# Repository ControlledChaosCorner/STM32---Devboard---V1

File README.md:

This Board uses an ST STM32F030C6T6TR MCU

Component list:

- 1 × 18pF capacitor (0603)
- 8 × 100nF capacitors (0603)
- 4 × 4.7µF capacitors (0603)
- 1 × 1nF capacitor (0603)
- 1 × 10µF capacitor (0805)
- 1 × 10nF capacitor (0603)
- 1 × 1µF capacitor (0805)
- 2 × LED (0603) — Power & PA15
- 1 × Fuse 1A (Plugin)
- 1 × USB Type-C receptacle (6-pin, power-only)
- 1 × SWD header (1×5, 2.54mm)
- 2 × Pin header (1×10, 2.54mm)
- 2 × Pin header (1×12, 2.54mm)
- 2 × 10k resistors (1206)
- 2 × 5.1k resistors (0603)
- 2 × 4.7k resistors (1206)
- 1 × 1.5k resistor (0603)
- 1 × 240Ω resistor (1206)
- 1 × Reset switch (SMD tactile)
- 1 × STM32F030C6 microcontroller (LQFP-48, 7×7mm, 0.5mm pitch)
- 1 × TLV70433 regulator (SOT-23-5)

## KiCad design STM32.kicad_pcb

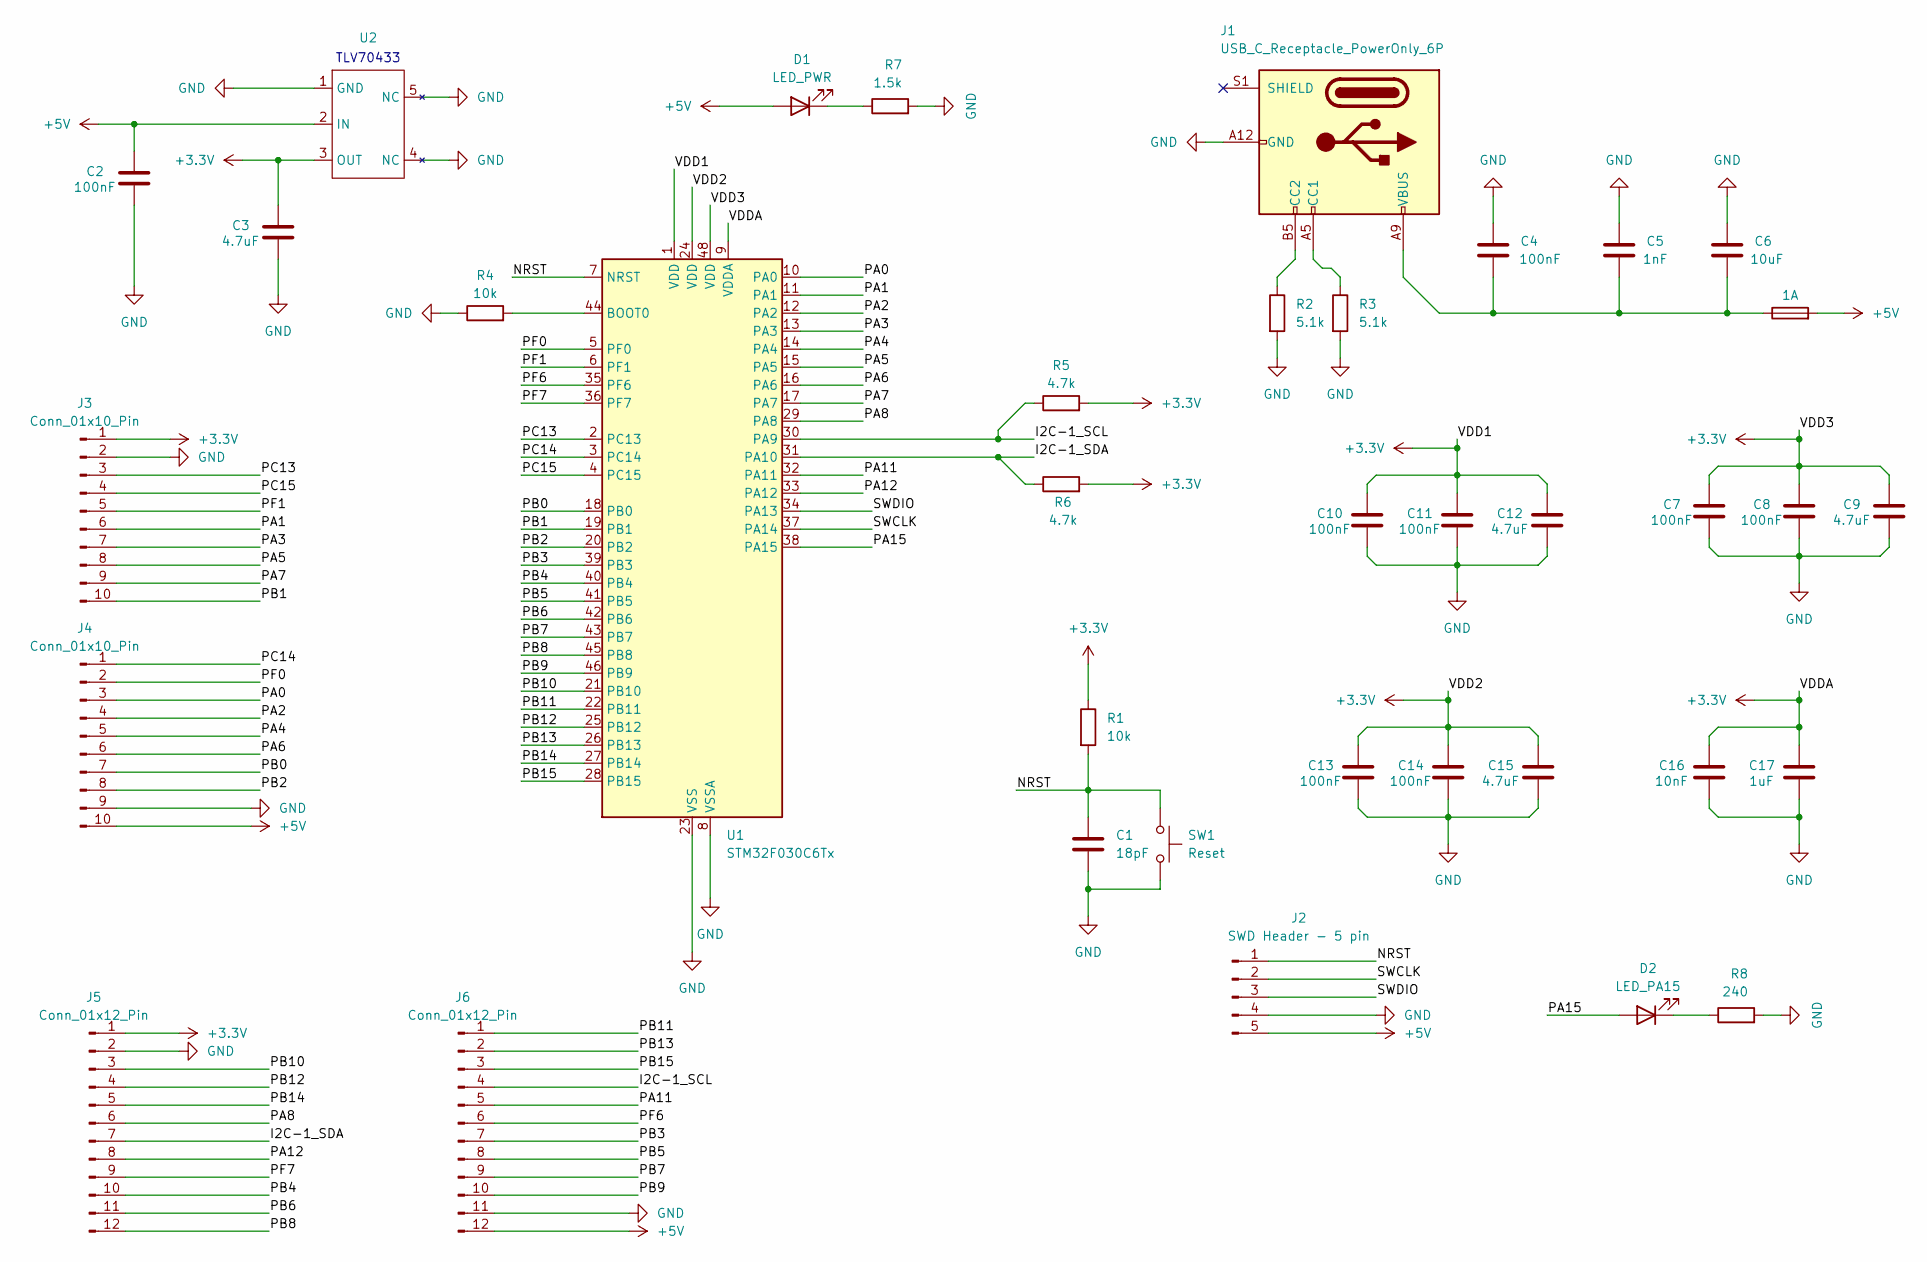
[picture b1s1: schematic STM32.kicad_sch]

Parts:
C1: 18pF; C_0603_1608Metric
C2, C4, C7, C8, C10, C11, C13, C14: 100nF; C_0603_1608Metric
C3, C9, C12, C15: 4.7uF; C_0603_1608Metric
C5: 1nF; C_0603_1608Metric
C6: 10uF; C_0805_2012Metric
C16: 10nF; C_0603_1608Metric
C17: 1uF; C_0805_2012Metric
D1: LED_PWR; LED_0603_1608Metric
D2: LED_PA15; LED_0603_1608Metric
F1: 1A; 1A Fuse
J1: USB_C_Receptacle_PowerOnly_6P; USB_C_Receptacle_GCT_USB4125-xx-x_6P_TopMnt_Horizontal
J2: SWD Header - 5 pin; PinHeader_1x05_P2.54mm_Vertical
J3, J4: Conn_01x10_Pin; PinHeader_1x10_P2.54mm_Vertical
J5, J6: Conn_01x12_Pin; PinHeader_1x12_P2.54mm_Vertical
R1, R4: 10k; R_1206_3216Metric
R2, R3: 5.1k; R_0603_1608Metric
R5, R6: 4.7k; R_1206_3216Metric
R7: 1.5k; R_0603_1608Metric
R8: 240; R_1206_3216Metric
SW1: Reset; SW_SPST_CK_RS282G05A3
U1: STM32F030C6Tx; LQFP-48_7x7mm_P0.5mm
U2: SOT-23-5

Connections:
+3.3V: C3.2, C7.2, C8.2, C9.2, C10.2, C11.2, C12.2, C13.2, C14.2, C15.2, C16.2, C17.2, J3.1, J5.1, R1.1, R5.2, R6.2, U1.1 (VDD), U1.9 (VDDA), U1.24 (VDD), U1.48 (VDD), U2.3 (OUT)
+5V: C2.2, D1.2 (A), F1.2, J2.5, J4.10, J6.12, U2.2 (IN)
/I2C-1_SCL: J6.4, R5.1, U1.30 (PA9)
/I2C-1_SDA: J5.7, R6.1, U1.31 (PA10)
/NRST: C1.1, J2.1, R1.2, SW1.1, U1.7 (NRST)
/PA0: J4.3, U1.10 (PA0)
/PA1: J3.6, U1.11 (PA1)
/PA2: J4.4, U1.12 (PA2)
/PA3: J3.7, U1.13 (PA3)
/PA4: J4.5, U1.14 (PA4)
/PA5: J3.8, U1.15 (PA5)
/PA6: J4.6, U1.16 (PA6)
/PA7: J3.9, U1.17 (PA7)
/PA8: J5.6, U1.29 (PA8)
/PA11: J6.5, U1.32 (PA11)
/PA12: J5.8, U1.33 (PA12)
/PA15: D2.2 (A), U1.38 (PA15)
/PB0: J4.7, U1.18 (PB0)
/PB1: J3.10, U1.19 (PB1)
/PB2: J4.8, U1.20 (PB2)
/PB3: J6.7, U1.39 (PB3)
/PB4: J5.10, U1.40 (PB4)
/PB5: J6.8, U1.41 (PB5)
/PB6: J5.11, U1.42 (PB6)
/PB7: J6.9, U1.43 (PB7)
/PB8: J5.12, U1.45 (PB8)
/PB9: J6.10, U1.46 (PB9)
/PB10: J5.3, U1.21 (PB10)
/PB11: J6.1, U1.22 (PB11)
/PB12: J5.4, U1.25 (PB12)
/PB13: J6.2, U1.26 (PB13)
/PB14: J5.5, U1.27 (PB14)
/PB15: J6.3, U1.28 (PB15)
/PC13: J3.3, U1.2 (PC13)
/PC14: J4.1, U1.3 (PC14)
/PC15: J3.4, U1.4 (PC15)
/PF0: J4.2, U1.5 (PF0)
/PF1: J3.5, U1.6 (PF1)
/PF6: J6.6, U1.35 (PF6)
/PF7: J5.9, U1.36 (PF7)
/SWCLK: J2.2, U1.37 (PA14)
/SWDIO: J2.3, U1.34 (PA13)
GND: C1.2, C2.1, C3.1, C4.1, C5.1, C6.1, C7.1, C8.1, C9.1, C10.1, C11.1, C12.1, C13.1, C14.1, C15.1, C16.1, C17.1, J1.A12 (GND), J1.B12 (GND), J2.4, J3.2, J4.9, J5.2, J6.11, R2.2, R3.2, R4.1, R7.2, R8.2, SW1.2, U1.8 (VSSA), U1.23 (VSS), U1.47 (VSS), U2.1 (GND), U2.4 (NC), U2.5 (NC)
unnamed: C4.2, C5.2, C6.2, F1.1, J1.A9 (VBUS), J1.B9 (VBUS)
unnamed: D1.1 (K), R7.1
unnamed: D2.1 (K), R8.1
unnamed: J1.A5 (CC1), R3.1
unnamed: J1.B5 (CC2), R2.1
unnamed: R4.2, U1.44 (BOOT0)

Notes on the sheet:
TLV70433

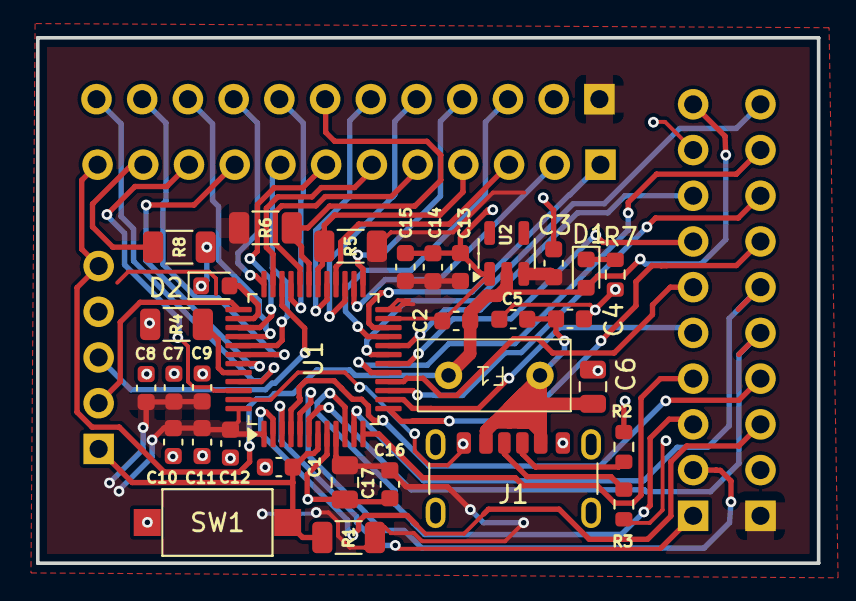
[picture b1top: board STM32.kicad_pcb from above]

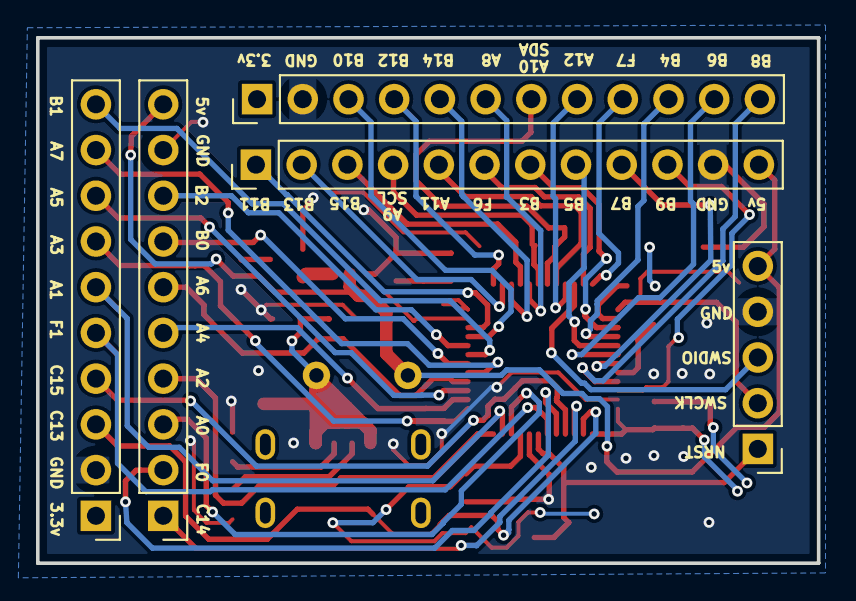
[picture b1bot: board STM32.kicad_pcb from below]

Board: 2 copper layers, 43.4 x 29.2 mm, 37 parts (5 on the bottom side), 49 nets.

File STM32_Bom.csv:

"Reference","Value","Datasheet","Footprint","Qty","DNP"
"C1","18pF","~","Capacitor_SMD:C_0603_1608Metric","1",""
"C2,C4,C7,C8,C10,C11,C13,C14","100nF","~","Capacitor_SMD:C_0603_1608Metric","8",""
"C3,C9,C12,C15","4.7uF","~","Capacitor_SMD:C_0603_1608Metric","4",""
"C5","1nF","~","Capacitor_SMD:C_0603_1608Metric","1",""
"C6","10uF","~","Capacitor_SMD:C_0805_2012Metric","1",""
"C16","10nF","~","Capacitor_SMD:C_0603_1608Metric","1",""
"C17","1uF","~","Capacitor_SMD:C_0805_2012Metric","1",""
"D1","LED_PWR","~","LED_SMD:LED_0603_1608Metric","1",""
"D2","LED_PA15","~","LED_SMD:LED_0603_1608Metric","1",""
"F1","1A","~","Library:1A Fuse","1",""
"J1","USB_C_Receptacle_PowerOnly_6P","https://www.usb.org/sites/default/files/documents/usb_type-c.zip","Connector_USB:USB_C_Receptacle_GCT_USB4125-xx-x_6P_TopMnt_Horizontal","1",""
"J2","SWD Header - 5 pin","~","Connector_PinHeader_2.54mm:PinHeader_1x05_P2.54mm_Vertical","1",""
"J3,J4","Conn_01x10_Pin","~","Connector_PinHeader_2.54mm:PinHeader_1x10_P2.54mm_Vertical","2",""
"J5,J6","Conn_01x12_Pin","~","Connector_PinHeader_2.54mm:PinHeader_1x12_P2.54mm_Vertical","2",""
"R1,R4","10k","~","Resistor_SMD:R_1206_3216Metric","2",""
"R2,R3","5.1k","~","Resistor_SMD:R_0603_1608Metric","2",""
"R5,R6","4.7k","~","Resistor_SMD:R_1206_3216Metric","2",""
"R7","1.5k","~","Resistor_SMD:R_0603_1608Metric","1",""
"R8","240","~","Resistor_SMD:R_1206_3216Metric","1",""
"SW1","Reset","~","Button_Switch_SMD:SW_SPST_CK_RS282G05A3","1",""
"U1","STM32F030C6Tx","https://www.st.com/resource/en/datasheet/stm32f030c6.pdf","Package_QFP:LQFP-48_7x7mm_P0.5mm","1",""
"U2","TLV70433","","Package_TO_SOT_SMD:SOT-23-5","1",""
